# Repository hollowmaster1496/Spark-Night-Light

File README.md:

# Spark-Night-Light
PCB for night light

## Intro

The Spark Night Light is an electronic circuit that turns on an LED in dim lighting conditions.

## Demo

Below is a simple demonstration of the LED turning on as all ambient lights in the room are turned off.

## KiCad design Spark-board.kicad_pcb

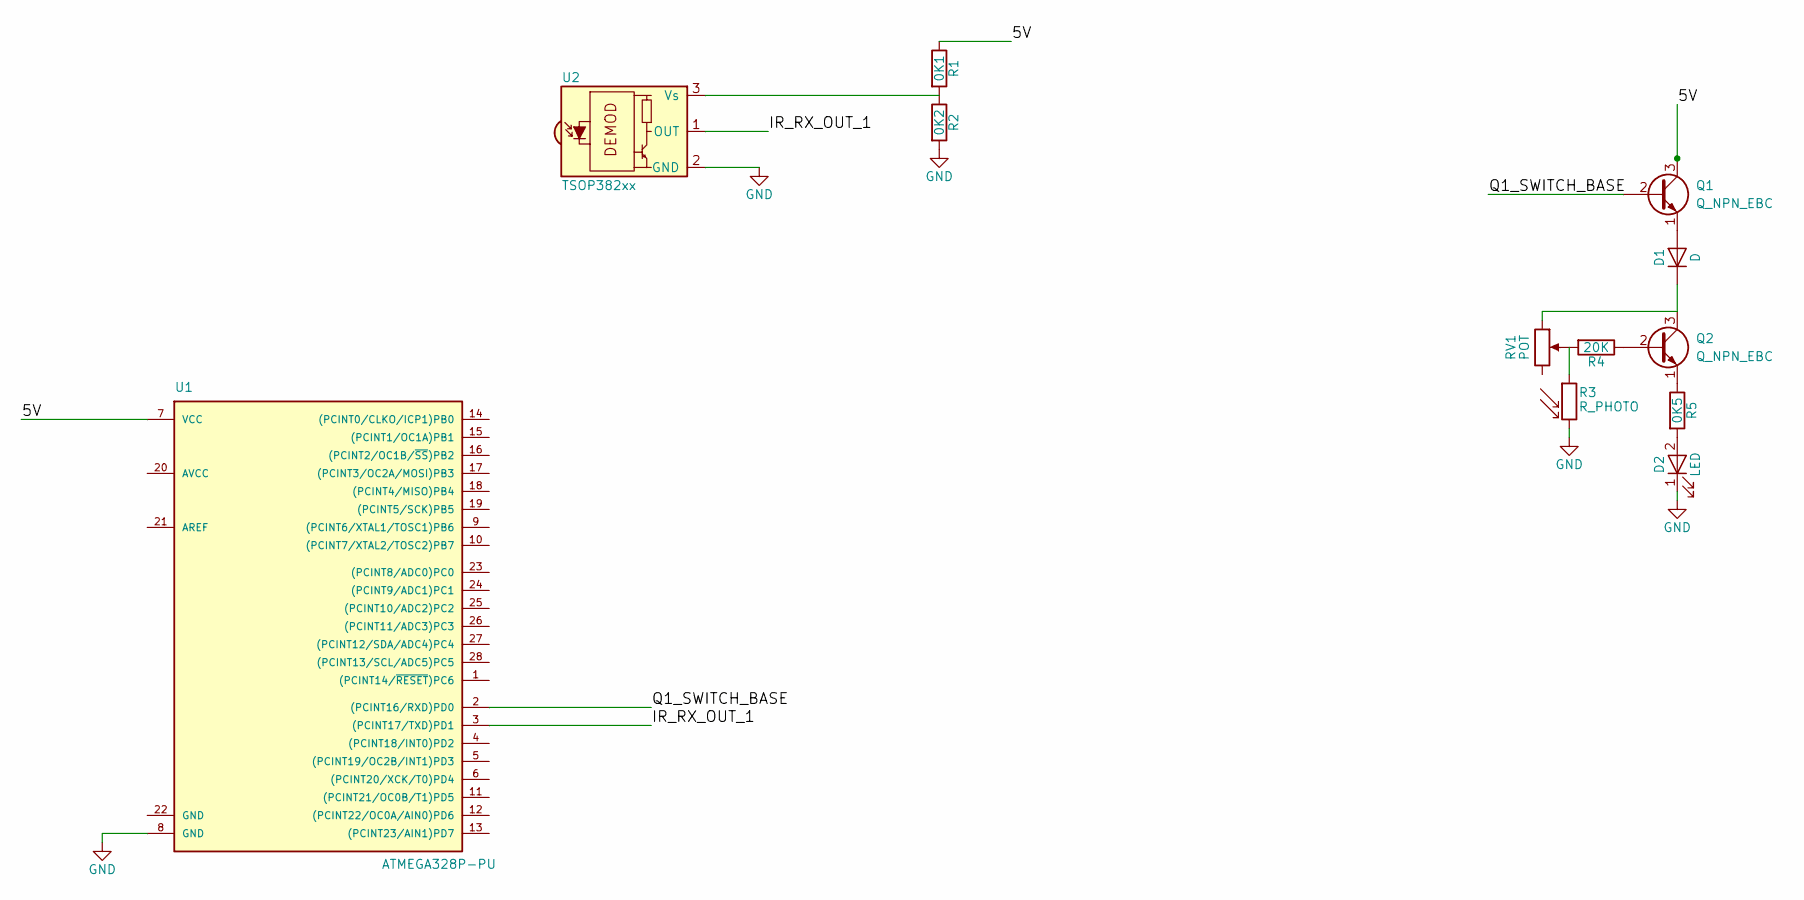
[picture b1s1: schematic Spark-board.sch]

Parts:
D1: D; D_0603
D2: LED; LED-L1T2_LUMILEDS
Q1, Q2: Q_NPN_EBC; TO92
R1: 0K1; R_0603_HandSoldering
R2: 0K2; R_0603_HandSoldering
R3: R_PHOTO; PHODET_PDV-P8103
R4: 20K; R_0603_HandSoldering
R5: 0K5; R_0603_HandSoldering
RV1: POT; Potentiometer_Alps_RK09K_Vertical
U1: ATMEGA328P-PU; DIP254P762X457-28
U2: TSOP382xx; IRReceiver_Vishay_MINICAST-3pin

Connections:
/5V: Q1.3 (C), R1.1, U1.7 (VCC)
/IR_RX_OUT_1: U1.3 ((PCINT17/TXD)PD1), U2.1 (OUT)
/Q1_SWITCH_BASE: Q1.2 (B), U1.2 ((PCINT16/RXD)PD0)
GND: D2.1 (K), R2.2, R3.2, U1.8 (GND), U2.2 (GND)
unnamed: D1.1 (K), Q2.3 (C), RV1.1
unnamed: D1.2 (A), Q1.1 (E)
unnamed: D2.2 (A), R5.2
unnamed: Q2.1 (E), R5.1
unnamed: Q2.2 (B), R4.1
unnamed: R1.2, R2.1, U2.3 (Vs)
unnamed: R3.1, R4.2, RV1.2

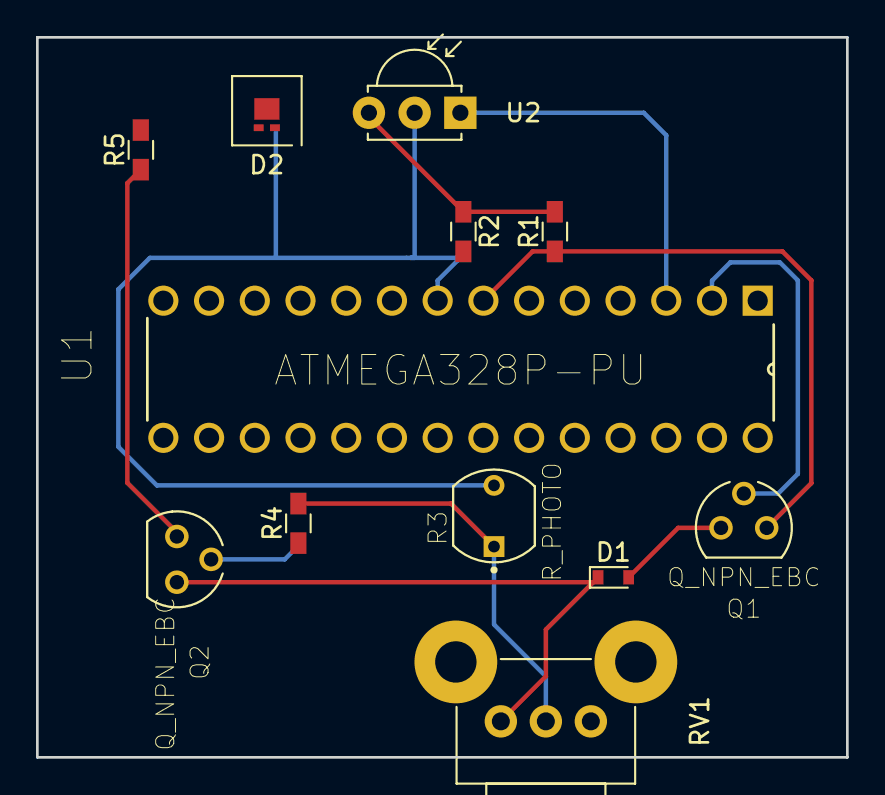
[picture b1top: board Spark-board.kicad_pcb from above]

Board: 2 copper layers, 45.0 x 40.0 mm, 12 parts (0 on the bottom side), 11 nets.

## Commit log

2018-11-12 Created new repo for Spark-board hardware in KiCad
2018-11-12 Created basic schematic layout for night-light
    Features:
    - photo-resistor and potentiometer to adjust current through LEDs under
    different lighting conditions
    - Transistor to switch off current through LEDs depending on level of light
    - Transistor to enable the system via AtMega32P uC.
2018-11-13 - Added hierarchal pin label 'Q1_SWITCH_BASE' and global pin '5V'
2018-11-19 - Assigned AVR uP pins to control NPN Transistor
    - Added IR Rx Module (TSOP382xx) to allow Power ON/OFF of system remotely
2018-11-19 - Added name and date details to Title Block
2018-11-19 - Annotated components
2018-11-19 - Added values to all resistors
    - IR Rx receiver: Voltage divider should provide ~3.3V at Vs input
    - Q1 Base: Voltage divider should provide adequate voltage to just keep LED off
    while ensure low current through transistor base
2018-11-27 Generated Netlist of Spark-Board schematic
2018-11-30 Imported new footprint libraries
    PN2222, ATMEGA328P-PU, PDV-P8103
2018-11-30 Generated netlist with new footprints
2018-11-30 Created PCB with component footprints
2018-12-03 Resolved overlapping ratsnest in pcbnew
2018-12-04 Re-arranged footprints for tighter fit
2018-12-04 Added Board outline
    Dimensions: 45 mm x 40 mm
2018-12-04 Added ground to one photo-resistor on schematic and re-generated netlist
2018-12-04 Added copper track segments to PCB and translated components to the left
2018-12-05 Added README.md and display image
2018-12-13 Added simple demo video with Breadboard circuit
2019-02-03 Readme.md: Updated image of PCB from 3d view to front view
2019-02-03 Fixed formatting in README.md
    - Added Intro
    # Conflicts:
    # README.md
